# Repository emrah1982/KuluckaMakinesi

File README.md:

# Kuluçka Makinesi — ESP32 Akıllı Kontrol Sistemi

ESP32 tabanlı, 11 hayvan profili destekleyen çok evreli kuluçka kontrol sistemi.
3.2" TFT dokunmatik ekran, web arayüzü ve OTA güncelleme içerir.

> Ayrıntılı kullanım için: [`KuluckaMakinesi_Esp32/KULLANIM_KILAVUZU.md`](KuluckaMakinesi_Esp32/KULLANIM_KILAVUZU.md)

---

## Donanım Bağlantıları

### ESP32 Pin Haritası

| Fonksiyon | Pin | Açıklama |
|-----------|-----|----------|
| I2C SDA | **IO32** | Tüm I2C cihazları (MUX üzerinden) |
| I2C SCL | **IO25** | Tüm I2C cihazları (MUX üzerinden) |
| Fan PWM | **IO18** | L298N `ENA` — 25 kHz (opsiyonel, aşağıya bak) |
| TFT arka ışık | IO27 | Ekran parlaklığı |
| Dokunmatik CS | IO33 | XPT2046 |
| Dokunmatik IRQ | IO36 | Dokunma algılama |
| SD kart CS | IO5 | MicroSD |
| Hoparlör | IO26 | Alarm sesi |
| Amplifikatör EN | IO4 | Hoparlör güç kontrolü |

### I2C Yapısı — Grove 8 Kanal Multiplexer (TCA9548A, `0x70`)

Tüm I2C cihazları tek bir multiplexer arkasındadır.

```
ESP32 (IO32 / IO25)
  │
  └── Grove 8 Kanal I2C MUX (0x70)
        ├── CH0 : DS3231 RTC        (0x68) + AT24C32 EEPROM (0x57)
        ├── CH1 : SHT40             (0x44)  birincil sıcaklık/nem
        ├── CH2 : SHT30             (0x44)  ikincil (füzyon/yedek)
        ├── CH3 : SCD30             (0x61)  CO2
        ├── CH4 : MLX90614ESF-BCC   (0x5A)  yumurta IR sıcaklık
        ├── CH5 : (boş)
        ├── CH6 : (boş)
        └── CH7 : PCF8574           (0x20)  röle kartı + yardımcı çıkışlar
```

**MUX adresi:** A0/A1/A2 pinleri GND'ye bağlıyken `0x70`. Adres değişse bile
firmware 0x70–0x77 arasını otomatik tarar; `MUX_ADDR` elle değiştirilmesi
gerekmez.

### PCF8574 Çıkışları (MUX CH7)

| Bit | Uç | Bağlantı | Not |
|-----|-----|----------|-----|
| P0 | Röle 1 | Isıtıcı | Active LOW |
| P1 | Röle 2 | Nemlendirici | Active LOW |
| P2 | Röle 3 | Çevirme motoru güç | Active LOW |
| P3 | Röle 4 | Çevirme motoru yön | Active LOW |
| P4 | — | A4988 `STEP` | Yalnızca `TURNER_TYPE=1` |
| P5 | — | A4988 `DIR` | Yalnızca `TURNER_TYPE=1` |
| P6 | — | A4988 `ENABLE` | Aktif LOW |
| P7 | — | **L298N `IN1`** | Fan enable |

> **Güvenli çıkış durumu `RELAY_ALL_OFF = 0x7F`.** Bit 7'nin **0** olması
> önemlidir: aksi halde "tüm çıkışlar kapalı" denen durumda L298N girişi
> enable konumunda kalır ve fanın durması tek bir sinyale bağlı olurdu.

### Röle Kartı Beslemesi

Röle modülünde **iki ayrı devre** vardır ve ikisi farklı beslenir:

| Devre | Uçlar | Ne yapar | Gerekli |
|-------|-------|----------|---------|
| **Mantık (giriş)** | `VCC` `GND` `IN1..IN4` | LED + optokuplör | ~5 mA |
| **Bobin (güç)** | `JD-VCC` `GND` | Rölenin kendisi | **5V, röle başına ~70 mA** |

Çoğu 4'lü modülde `JD-VCC | VCC | GND` şeklinde 3 pinli bir başlık ve
üzerinde bir jumper bulunur. Jumper takılıyken bobinler `VCC` üzerinden
beslenir; çıkarıldığında `JD-VCC`'ye **ayrı 5V** vermek gerekir.

#### "LED yanıyor ama röle tıklamıyor"

Bu belirti, giriş devresinin çalıştığını ama **bobin devresinin
beslenmediğini** söyler. Sırayla kontrol edin:

1. **`VCC` gerçekten 5V mu?** 3.3V ile beslenirse LED yanar (~2V yeter) ama
   5V'luk röle bobini çekmez. En sık sebep budur.
2. **`JD-VCC` jumper'ı takılı mı?** Değilse `JD-VCC`'ye ayrı 5V verin.
3. **Harici 5V'un GND'si ortak mı?** Bobin devresinin dönüş yolu yoksa
   optokuplör iletse bile röle çekmez. Harici beslemenin eksi ucu
   ESP32/PCF8574 toprağına bağlanmalıdır.
4. **Akım yetiyor mu?** 4 röle aynı anda ~280 mA çeker. ESP32 kartının
   regülatöründen beslenirse yetmez, ayrı besleme gerekir.

**Ölçüm:** `JD-VCC` ile `GND` arasında ~5V okumalısınız. 3.3V okuyorsanız
sorun budur.

> Röle kartına yazma işleminin gerçekten geçtiğini yazılım tarafından
> doğrulamak için Kontrol sekmesindeki **ROLE / CIKIS TESTI**'ni kullanın.
> Modaldeki `Role karti: OK` satırı I2C yazmasının başarılı olduğunu
> gösterir — bu satır OK iken röle tıklamıyorsa sorun kesinlikle besleme
> tarafındadır.

### Fan Bağlantısı (L298N)

Fan röle üzerinden değil, L298N motor sürücü kartı üzerinden çalışır.

| # | Kaynak | L298N ucu | İşlev |
|---|--------|-----------|-------|
| 1 | PCF8574 **P7** | `IN1` | Enable — **zorunlu** |
| 2 | Sistem **GND** | `IN2` | Yön sabitleme — **zorunlu** |
| 3 | ESP32 **IO18** | `ENA` | Hız PWM — opsiyonel |
| 4 | Sistem **GND** | `GND` | **Ortak toprak — zorunlu** |
| 5 | 12V (+) | `+12V` | Motor beslemesi |
| 6 | 12V (−) | `GND` | Motor beslemesi dönüşü |

**`IN1` LOW iken motor dönmez**, `ENA` ne olursa olsun.

#### Ortak toprak — en sık atlanan nokta

`IN2`'yi PCF8574'ün GND'sine bağlamak **doğrudur**, ama tek başına yetmez:

> **L298N'in kendi `GND` terminali de aynı toprağa bağlanmalıdır.**

Sebebi: `IN1`'e gelen "HIGH" sinyali PCF8574'ün toprağına göre ölçülür.
L298N kendi girişlerini kendi `GND` pinine göre değerlendirir. Bu ikisi
birbirine bağlı değilse sinyalin referansı yoktur ve sürücü girişleri
tanımsız davranır — motor hiç dönmeyebilir veya rastgele davranabilir.

Pratikte tek kural: **ESP32, PCF8574, L298N ve 12V beslemenin eksi ucu —
dördü de aynı toprak noktasında buluşmalı.** Bu sağlandıktan sonra `IN2`'yi
bu topraktan herhangi birine bağlayabilirsiniz; PCF8574'ün GND'si de olur.

#### Sinyal seviyesi

PCF8574 3.3V ile beslenir ve çıkışları *quasi-bidirectional*'dır: HIGH
durumu zayıf bir dahili pull-up ile sağlanır (~100 µA). L298N'in mantık
girişi 3.3V'u HIGH olarak kabul eder, ancak akım marjı dardır.

> **Öneri:** `IN1` ile 3.3V arasına **4.7 kΩ** pull-up direnci ekleyin.
> PCF8574 LOW yazarken güçlü şekilde (25 mA'e kadar) çeker, HIGH yazarken
> dış direnç seviyeyi sağlam tutar. Uzun veya gürültülü kabloda bu fark
> yaratır.

#### İki kurulum seçeneği

`Config.h` içindeki `FAN_SPEED_CONTROL` buna göre ayarlanır:

| | Sadece P7 (`= 0`) | P7 + IO18 (`= 1`) |
|---|---|---|
| Sinyal kablosu | 1 | 2 |
| L298N `ENA` jumper'ı | **Takılı kalır** | **Çıkarılır** |
| Fan hızı | Tek hız (tam) | 0–255 arası |
| Sıcaklığa bağlı hız eğrisi | İşlevsiz | Çalışır |

> `ENA` jumper'ını çıkarmayı unutursanız `ENA` sürekli 5V'ta kalır ve
> IO18'den gelen PWM hiçbir etki yapmaz — fan hep tam hızda döner.

> **P7 ile hız ayarı yapılamaz.** P7 bir I2C genişletici pinidir; her seviye
> değişimi bir I2C işlemidir (100 kHz'de ~1 ms). Ulaşılabilecek frekans birkaç
> yüz Hz mertebesinde kalır — fan için gereken 25 kHz'in çok altında. Üstelik
> aynı hat RTC, sensörler ve röleleri de taşıdığı için bus tıkanır. Hız
> kontrolü ancak ESP32'nin donanım PWM çıkışı ile mümkündür.

---

## Yapılandırma (`Config.h`)

Sık değiştirilen anahtarlar:

| Sabit | Varsayılan | Açıklama |
|-------|-----------|----------|
| `DEBUG_ENABLED` | `1` | Seri monitörde periyodik `[STATUS]` satırı |
| `FAN_SPEED_CONTROL` | `1` | `0` = ENA kablosu yok, tek hız |
| `FAN_DUTY_MODE` | `0` | `1` = fan kesintili çalışır |
| `RELAY_TEST_ENABLED` | `1` | Röle test modu (devreye alma sonrası `0` yapın) |
| `TURNER_TYPE` | `0` | `0` = DC/röle, `1` = step motor |
| `SD_ENABLED` | `1` | SD kart veri kaydı |

### Fan kesintili çalışma

`FAN_DUTY_MODE = 1` yapıldığında fan her `FAN_DUTY_PERIOD_SEC` (5 dk) içinde
`FAN_DUTY_ON_SEC` (1 dk) çalışır, kalan sürede durur.

> **Kuluçkaya özgü uyarı:** Fan yalnızca soğutma değil, aynı zamanda
> **homojenlik** aracıdır. Uzun süre durursa kabin içinde katmanlaşma olur
> (üst sıcak, alt soğuk); sensör kendi bölgesini ölçer ve tepsinin geri kalanı
> hedeften sapabilir. Bu yüzden kesinti "tamamen kapalı" değil, **her periyotta
> garanti sirkülasyon** olarak tasarlandı. Ayrıca sıcaklık hedefi
> `FAN_DUTY_FORCE_DELTA` kadar aşarsa fan kesintisiz çalışmaya döner.

---

## Derleme

Arduino IDE ayarları:

- **Kart:** ESP32 Dev Module
- **Partition Scheme:** menüden seçmeye gerek yok — sketch klasöründeki
  `partitions.csv` kullanılır (2 × 1.9 MB app + OTA destekli). Menüden
  seçilecekse *Minimal SPIFFS (1.9MB APP with OTA)*.
  **"Huge APP" seçmeyin**, OTA bölümü yoktur.

Gerekli kütüphaneler:

```
RTClib (Adafruit)          TFT_eSPI
ESPAsyncWebServer          AsyncTCP  (mathieucarbou sürümleri)
```

---

## Güvenlik Katmanları

| Katman | Eşik / Koşul | Aksiyon |
|--------|--------------|---------|
| Aşırı sıcaklık | ≥ 40 °C | Acil kapatma |
| Kritik düşük sıcaklık | < 25 °C, 2 dk | Acil kapatma |
| Sensör arızası | 5 ardışık hata | Acil kapatma |
| Röle yazma hatası | 3 ardışık hata | `ALARM_IO_FAIL` + kaçış modu |
| **Termal kaçış** | Kapatmadan 90 sn sonra sıcaklık düşmüyor | Fan tam güç + kalıcı alarm |
| I2C kilitlenme | 3 ardışık kanal hatası | Otomatik bus kurtarma |

> **Termal kaçış**, röle kontağının yapışması durumudur. Yazılımın yapabileceği
> bir şey kalmaz — ısıtıcı beslemesini elle kesmek gerekir. Bu senaryoya karşı
> gerçek koruma, yazılımdan bağımsız bir **donanım termostatı** takmaktır.

---

## Depo Yapısı

```
KuluckaMakinesi/
├── KuluckaMakinesi_Esp32/
│   ├── KuluckaMakinesi/            Ana firmware
│   ├── KuluckaMakinesi_Yumurta_Esp32/  Uzak yumurta IR cihazı (opsiyonel)
│   ├── I2CScanner/                 I2C tanılama eskizi
│   └── KULLANIM_KILAVUZU.md        Ayrıntılı kullanım kılavuzu
├── KuluckaMakinesi_kicad/          Devre şeması ve PCB
├── docker/                         Geliştirme için sahte sunucu
├── data/ · db/                     Web arayüzü varlıkları, örnek veri
└── docs/                           Tasarım notları
```

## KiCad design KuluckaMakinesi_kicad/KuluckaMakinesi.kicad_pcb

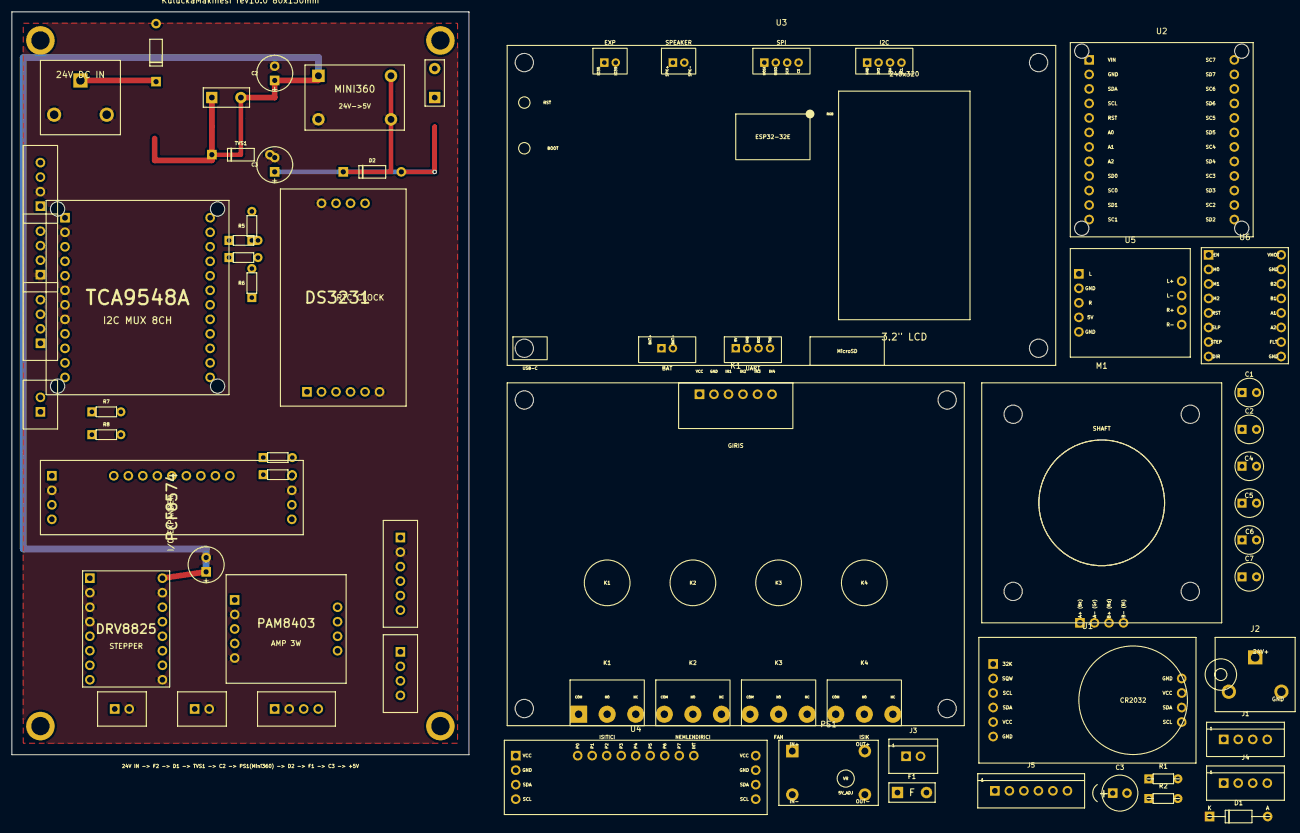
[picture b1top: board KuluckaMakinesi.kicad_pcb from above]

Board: 2 copper layers, 80.0 x 130.0 mm, 61 parts (0 on the bottom side), 28 nets.

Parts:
C1: 100uF/25V; CP_Radial_D6.3mm_P2.5mm
C1#2, C2#2, C4, C5, C6, C7: 100nF; C_Disc_D5mm_P2.54mm
C2, C3#2: 100uF/35V; CP_Radial_D6.3mm_P2.5mm
C3: 100uF/16V; CP_Radial_D6.3mm_P2.5mm
D1, D1#2: SS34; D_Axial_DO41_P10.16mm
D2: SS14; D_Axial_DO41_P10.16mm
F1: 1A_PTC; F_Polyfuse_Radial_P5.08mm
F1#2, F2: 3A_PTC; F_Polyfuse_Radial_P5.08mm
H1, H2, H3, H4: M3; MountingHole_3.2mm_M3
J1: SHT40_SENSOR; JST_XH_4pin_2.54mm
J1#2: 24V_IN; DC_Jack_5.5x2.1
J2: DC_Jack_24V_5.5x2.1; DC_Jack_5.5x2.1
J2#2: BAT_2p; JST_XH_2pin_2.54mm
J3: 12V_VMOT; JST_XH_2pin_2.54mm
J3#2: UART_4p; JST_XH_4pin_2.54mm
J4: I2C_4p; JST_XH_4pin_2.54mm
J4#2: NEMA17_MOTOR; JST_XH_4pin_2.54mm
J5: ROLE_CTRL_6p; JST_XH_6pin_2.54mm
J5#2: EXP_2p; JST_XH_2pin_2.54mm
J6: SPI_4p; JST_XH_4pin_2.54mm
J7: SPK_2p; JST_XH_2pin_2.54mm
J8: NEMA17_4p; JST_XH_4pin_2.54mm
J9: RELAY_6p; JST_XH_6pin_2.54mm
J10: SHT40_4p; JST_XH_4pin_2.54mm
K1: RELAY_4CH; Relay4Channel_Module
M1: NEMA17; NEMA17_42x42_Mount
PS1: MINI360; Mini360_Buck
PS1#2: Mini360_24V_5V; Mini360_Buck
R1, R1#2, R2, R2#2, R3, R4, R5, R6, R7, R8: 4.7k; R_Axial_P5.08mm
TVS1: P6KE30A; D_Axial_DO41_P10.16mm
U1, U4: DS3231; DS3231_Module
U2, U2#2: TCA9548A; TCA9548A_Module
U3: ESP32_TFT; ESP32_TFT_3248S032
U4#2, U5#2: PCF8574; PCF8574_Module
U5, U7: PAM8403; PAM8403_Module
U6, U6#2: DRV8825; DRV8825_Module

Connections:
/+3V3: J4.2, J10.1, R1#2.1, R2.1, R3.1, R4.1, R5.1, R6.1, R7.1, R8.1, U2.1, U2.5, U4.5, U4.8, U5#2.1, U5#2.5, U6.5, U6.6
/+5V: C3.1, F1.2, J3#2.1, J9.1, U7.4
/+5V_BUCK: D2.1, PS1.3
/+5V_RAW: D2.2, F1.1
/+24V_FUSED: C1.1, C2.1, F2.2, PS1.1, TVS1.1, U6.9
/+24V_IN: D1.1, J1#2.1
/+24V_RAW: D1.2, F2.1
/AUDIO_IN: J7.1, U7.1, U7.3
/DIR: U5#2.15, U6.8
/GND: C1.2, C2.2, C3.2, J1#2.2, J2#2.2, J3#2.2, J4.1, J7.2, J9.2, J10.2, PS1.2, PS1.4, TVS1.2, U2.2, U2.6, U2.7, U2.8, U4.6, U4.7, U5#2.2, U5#2.6, U6.2, U6.3, U6.4, U6.10, U6.16, U7.2, U7.5
/I2C_SCL_CH0: J10.4, R4.2, U2.10
/I2C_SCL_CH1: R6.2, U2.12, U4.3, U4.10
/I2C_SCL_CH2: R8.2, U2.14, U5#2.4, U5#2.8
/I2C_SCL_MAIN: J4.4, R2.2, U2.4
/I2C_SDA_CH0: J10.3, R3.2, U2.9
/I2C_SDA_CH1: R5.2, U2.11, U4.4, U4.9
/I2C_SDA_CH2: R7.2, U2.13, U5#2.3, U5#2.7
/I2C_SDA_MAIN: J4.3, R1#2.2, U2.3
/MOT_A1: J8.1, U6.13
/MOT_A2: J8.2, U6.14
/MOT_B1: J8.3, U6.12
/MOT_B2: J8.4, U6.11
/MOT_EN: U5#2.13, U6.1
/RELAY_FAN: J9.5, U5#2.11
/RELAY_HEATER: J9.3, U5#2.9
/RELAY_HUMID: J9.4, U5#2.10
/RELAY_LIGHT: J9.6, U5#2.12
/STEP: J6.1, U6.7
